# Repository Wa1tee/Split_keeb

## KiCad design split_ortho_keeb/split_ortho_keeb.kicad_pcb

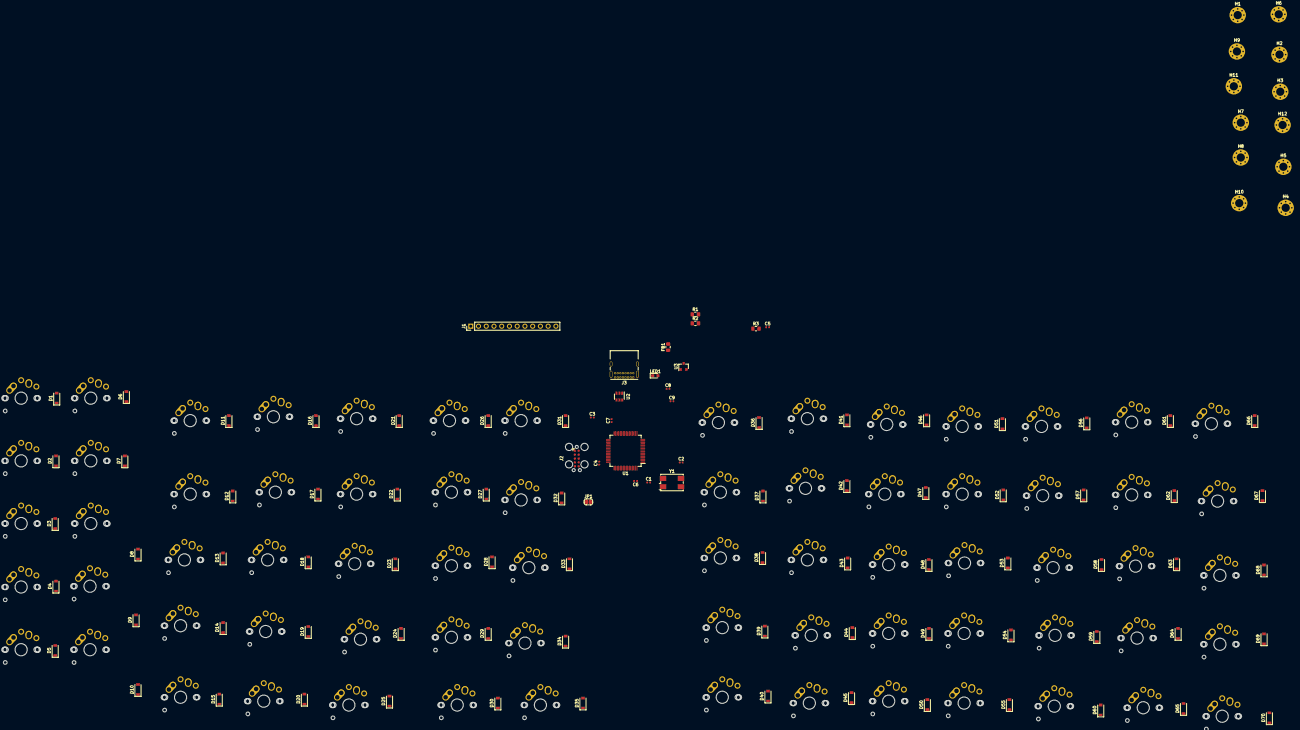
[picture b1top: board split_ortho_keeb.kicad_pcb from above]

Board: 2 copper layers, 174 parts (0 on the bottom side), 116 nets, no tracks yet.

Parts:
C1, C2: 30p; C_0402_1005Metric
C3: 4u7; C_0402_1005Metric
C4, C5, C6, C7: 100n; C_0402_1005Metric
C8, C9: 1u; C_0402_1005Metric
D1, D2, D3, D4, D5, D6, D7, D8, D9, D10, D11, D12, D13, D14, D15, D16, D17, D18, D19, D20, D21, D22, D23, D24, D25, D26, D27, D28, D29, D30, D31, D32, D33, D34, D35, D36, D37, D38, D39, D40, D41, D42, D43, D44, D45, D46, D47, D48, D49, D50, D51, D52, D53, D54, D55, D56, D57, D58, D59, D60, D61, D62, D63, D64, D65, D66, D67, D68, D69, D70: D; D_SOD-123
FB1: 100R; L_0805_2012Metric_Pad1.15x1.40mm_HandSolder
H1, H2, H3, H4, H5, H6, H7, H8, H9, H10, H11, H12: MountingHole_Pad; MountingHole_2.7mm_M2.5_Pad_Via
J1: CONN_LCD; PinHeader_1x12_P2.54mm_Vertical
J2: TC2050-IDC; Tag-Connect_TC2050-IDC-FP_2x05_P1.27mm_Vertical
J3: USB_C_Receptacle_USB2.0; USB_C_Receptacle_GCT_USB4085
JP1: SolderJumper_2_Open; SolderJumper-2_P1.3mm_Open_RoundedPad1.0x1.5mm
LED1: LED; LED_0603_1608Metric_Pad1.05x0.95mm_HandSolder
R1, R2, R3: 1k5; R_0805_2012Metric_Pad1.15x1.40mm_HandSolder
SW1, SW2, SW3, SW4, SW5, SW6, SW7, SW8, SW9, SW10, SW11, SW12, SW13, SW14, SW15, SW16, SW17, SW18, SW19, SW20, SW21, SW22, SW23, SW24, SW25, SW26, SW27, SW28, SW29, SW30, SW31, SW32, SW33, SW34, SW35, SW36, SW37, SW38, SW39, SW40, SW41, SW42, SW43, SW44, SW45, SW46, SW47, SW48, SW49, SW50, SW51, SW52, SW53, SW54, SW55, SW56, SW57, SW58, SW59, SW60, SW61, SW62, SW63, SW64, SW65, SW66, SW67, SW68, SW69, SW70: SW_Push; MX-Alps-Choc-1U-NoLED
U1: STM32F303RCTx; LQFP-64_10x10mm_P0.5mm
U2: USBLC6-2SC6; SOT-23-6
U3: XC6206P332MR; SOT-23
Y1: 32MHz; Crystal_SMD_7050-4Pin_7.0x5.0mm

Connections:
+3V3: C3.1, C4.1, C5.1, C6.1, C7.1, C9.1, J1.3, J2.1, JP1.1, LED1.2, R2.1, U1.19, U1.32, U1.48, U1.64, U3.2
+5V: FB1.2, J3.A4, J3.A9, J3.B4, J3.B9, U2.5
Col0: SW1.2, SW2.2, SW3.2, SW4.2, SW5.2, U1.55
Col1: SW6.2, SW7.2, SW8.2, SW9.2, SW10.2, U1.56
Col2: SW11.2, SW12.2, SW13.2, SW14.2, SW15.2, U1.57
Col3: SW16.2, SW17.2, SW18.2, SW19.2, SW20.2, U1.58
Col4: SW21.2, SW22.2, SW23.2, SW24.2, SW25.2, U1.59
Col5: SW26.2, SW27.2, SW28.2, SW29.2, SW30.2, U1.61
Col6: SW31.2, SW32.2, SW33.2, SW34.2, SW35.2, U1.62
Col7: SW36.2, SW37.2, SW38.2, SW39.2, SW40.2, U1.36, U1.54
Col8: SW41.2, SW42.2, SW43.2, SW44.2, SW45.2, U1.37
Col9: SW46.2, SW47.2, SW48.2, SW49.2, SW50.2, U1.38
Col10: SW51.2, SW52.2, SW53.2, SW54.2, SW55.2, U1.39
Col11: SW56.2, SW57.2, SW58.2, SW59.2, SW60.2, U1.40
Col12: SW61.2, SW62.2, SW63.2, SW64.2, SW65.2, U1.41
Col13: SW66.2, SW67.2, SW68.2, SW69.2, SW70.2, U1.42
GND: C1.2, C2.2, C3.2, C4.2, C5.2, C6.2, C7.2, C8.2, C9.2, H1.1, H2.1, H3.1, H4.1, H5.1, H6.1, H7.1, H8.1, H9.1, H10.1, H11.1, H12.1, J1.1, J2.3, J3.A1, J3.A12, J3.B1, J3.B12, R1.2, R3.2, U1.31, U1.47, U1.63, U2.2, U3.1, Y1.2, Y1.4
HSE_IN: C1.1, U1.5, Y1.1
HSE_OUT: C2.1, U1.6, Y1.3
LCD_CS: J1.10, U1.24
LCD_DC: J1.11, U1.25
LCD_LED: J1.2, U1.17
LCD_RST: J1.12, U1.26
NRST: J2.10, U1.7
unnamed: C8.1, FB1.1, U3.3
unnamed: D1.2, SW1.1
unnamed: D2.2, SW2.1
unnamed: D3.2, SW3.1
unnamed: D4.2, SW4.1
unnamed: D5.2, SW5.1
unnamed: D6.2, SW6.1
unnamed: D7.2, SW7.1
unnamed: D8.2, SW8.1
unnamed: D9.2, SW9.1
unnamed: D10.2, SW10.1
unnamed: D11.2, SW11.1
unnamed: D12.2, SW12.1
unnamed: D13.2, SW13.1
unnamed: D14.2, SW14.1
unnamed: D15.2, SW15.1
unnamed: D16.2, SW16.1
unnamed: D17.2, SW17.1
unnamed: D18.2, SW18.1
unnamed: D19.2, SW19.1
unnamed: D20.2, SW20.1
unnamed: D21.2, SW21.1
unnamed: D22.2, SW22.1
unnamed: D23.2, SW23.1
unnamed: D24.2, SW24.1
unnamed: D25.2, SW25.1
unnamed: D26.2, SW26.1
unnamed: D27.2, SW27.1
unnamed: D28.2, SW28.1
unnamed: D29.2, SW29.1
unnamed: D30.2, SW30.1
unnamed: D31.2, SW31.1
unnamed: D32.2, SW32.1
unnamed: D33.2, SW33.1
unnamed: D34.2, SW34.1
unnamed: D35.2, SW35.1
unnamed: D36.2, SW36.1
unnamed: D37.2, SW37.1
unnamed: D38.2, SW38.1
unnamed: D39.2, SW39.1
unnamed: D40.2, SW40.1
unnamed: D41.2, SW41.1
unnamed: D42.2, SW42.1
unnamed: D43.2, SW43.1
unnamed: D44.2, SW44.1
unnamed: D45.2, SW45.1
unnamed: D46.2, SW46.1
unnamed: D47.2, SW47.1
unnamed: D48.2, SW48.1
unnamed: D49.2, SW49.1
unnamed: D50.2, SW50.1
unnamed: D51.2, SW51.1
unnamed: D52.2, SW52.1
unnamed: D53.2, SW53.1
unnamed: D54.2, SW54.1
unnamed: D55.2, SW55.1
unnamed: D56.2, SW56.1
unnamed: D57.2, SW57.1
unnamed: D58.2, SW58.1
unnamed: D59.2, SW59.1
unnamed: D60.2, SW60.1
unnamed: D61.2, SW61.1
unnamed: D62.2, SW62.1
unnamed: D63.2, SW63.1
unnamed: D64.2, SW64.1
unnamed: D65.2, SW65.1
unnamed: D66.2, SW66.1
unnamed: D67.2, SW67.1
unnamed: D68.2, SW68.1
unnamed: D69.2, SW69.1
unnamed: D70.2, SW70.1
unnamed: JP1.2, R1.1, U1.60
unnamed: LED1.1, R3.1
Row0: D1.1, D6.1, D11.1, D16.1, D21.1, D26.1, D31.1, D36.1, D41.1, D46.1, D51.1, D56.1, D61.1, D66.1, U1.8
Row1: D2.1, D7.1, D12.1, D17.1, D22.1, D27.1, D32.1, D37.1, D42.1, D47.1, D52.1, D57.1, D62.1, D67.1, U1.9
Row2: D3.1, D8.1, D13.1, D18.1, D23.1, D28.1, D33.1, D38.1, D43.1, D48.1, D53.1, D58.1, D63.1, D68.1, U1.10
Row3: D4.1, D9.1, D14.1, D19.1, D24.1, D29.1, D34.1, D39.1, D44.1, D49.1, D54.1, D59.1, D64.1, D69.1, U1.11
Row4: D5.1, D10.1, D15.1, D20.1, D25.1, D30.1, D35.1, D40.1, D45.1, D50.1, D55.1, D60.1, D65.1, D70.1, U1.14
SPI_MISO: J1.7, U1.22
SPI_MOSI: J1.8, U1.23
SPI_SCK: J1.9, U1.21
SWCLK: J2.4, U1.49
SWDIO: J2.2, U1.46
SWO: J2.6, U1.15
TS_BSY: J1.5, U1.18
TS_CS: J1.6, U1.20
UART_RX: J2.7, U1.52
UART_TX: J2.8, U1.51
USBD+: R2.2, U1.45, U2.6
USBD-: U1.44, U2.4
USB_D+: J3.A6, J3.B6, U2.1
USB_D-: J3.A7, J3.B7, U2.3

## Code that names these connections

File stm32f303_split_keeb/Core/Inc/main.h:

/* USER CODE BEGIN Header */
/**
  ******************************************************************************
  * @file           : main.h
  * @brief          : Header for main.c file.
  *                   This file contains the common defines of the application.
  ******************************************************************************
  * @attention
  *
  * <h2><center>&copy; Copyright (c) 2020 STMicroelectronics.
  * All rights reserved.</center></h2>
  *
  * This software component is licensed by ST under BSD 3-Clause license,
  * the "License"; You may not use this file except in compliance with the
  * License. You may obtain a copy of the License at:
  *                        opensource.org/licenses/BSD-3-Clause
  *
  ******************************************************************************
  */
/* USER CODE END Header */

/* Define to prevent recursive inclusion -------------------------------------*/
#ifndef __MAIN_H
#define __MAIN_H

#ifdef __cplusplus
extern "C" {
#endif

/* Includes ------------------------------------------------------------------*/
#include "stm32f3xx_hal.h"

/* Private includes ----------------------------------------------------------*/
/* USER CODE BEGIN Includes */

/* USER CODE END Includes */

/* Exported types ------------------------------------------------------------*/
/* USER CODE BEGIN ET */

/* USER CODE END ET */

/* Exported constants --------------------------------------------------------*/
/* USER CODE BEGIN EC */

/* USER CODE END EC */

/* Exported macro ------------------------------------------------------------*/
/* USER CODE BEGIN EM */

/* USER CODE END EM */

/* Exported functions prototypes ---------------------------------------------*/
void Error_Handler(void);

/* USER CODE BEGIN EFP */

/* USER CODE END EFP */

/* Private defines -----------------------------------------------------------*/
#define Row0_Pin GPIO_PIN_0
#define Row0_GPIO_Port GPIOC
#define Row1_Pin GPIO_PIN_1
#define Row1_GPIO_Port GPIOC
#define Row2_Pin GPIO_PIN_2
#define Row2_GPIO_Port GPIOC
#define Row3_Pin GPIO_PIN_3
#define Row3_GPIO_Port GPIOC
#define Row4_Pin GPIO_PIN_0
#define Row4_GPIO_Port GPIOA
#define SWO_Pin GPIO_PIN_1
#define SWO_GPIO_Port GPIOA
#define LCD_RST_Pin GPIO_PIN_3
#define LCD_RST_GPIO_Port GPIOA
#define TS_BUSY_Pin GPIO_PIN_4
#define TS_BUSY_GPIO_Port GPIOF
#define LCD_CS_Pin GPIO_PIN_4
#define LCD_CS_GPIO_Port GPIOA
#define TS_CS_Pin GPIO_PIN_4
#define TS_CS_GPIO_Port GPIOC
#define TS_BUSYC5_Pin GPIO_PIN_5
#define TS_BUSYC5_GPIO_Port GPIOC
#define LCD_LED_Pin GPIO_PIN_0
#define LCD_LED_GPIO_Port GPIOB
#define Col7_Pin GPIO_PIN_15
#define Col7_GPIO_Port GPIOB
#define Col8_Pin GPIO_PIN_6
#define Col8_GPIO_Port GPIOC
#define Col9_Pin GPIO_PIN_7
#define Col9_GPIO_Port GPIOC
#define Col10_Pin GPIO_PIN_8
#define Col10_GPIO_Port GPIOC
#define Col11_Pin GPIO_PIN_9
#define Col11_GPIO_Port GPIOC
#define Col12_Pin GPIO_PIN_8
#define Col12_GPIO_Port GPIOA
#define Col13_Pin GPIO_PIN_9
#define Col13_GPIO_Port GPIOA
#define Col0_Pin GPIO_PIN_3
#define Col0_GPIO_Port GPIOB
#define Col1_Pin GPIO_PIN_4
#define Col1_GPIO_Port GPIOB
#define Col2_Pin GPIO_PIN_5
#define Col2_GPIO_Port GPIOB
#define Col3_Pin GPIO_PIN_6
#define Col3_GPIO_Port GPIOB
#define Col4_Pin GPIO_PIN_7
#define Col4_GPIO_Port GPIOB
#define Col5_Pin GPIO_PIN_8
#define Col5_GPIO_Port GPIOB
#define Col6_Pin GPIO_PIN_9
#define Col6_GPIO_Port GPIOB
/* USER CODE BEGIN Private defines */

/* USER CODE END Private defines */

#ifdef __cplusplus
}
#endif

#endif /* __MAIN_H */

/************************ (C) COPYRIGHT STMicroelectronics *****END OF FILE****/

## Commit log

2020-12-03 Added gitignore
2020-12-03 Added kicad files
2020-12-03 added stm32cubeide files
2020-12-04 fixed some button placements
